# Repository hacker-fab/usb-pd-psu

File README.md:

# USB PD PSU
Inspired by the [PocketPD project](https://github.com/CentyLab/PocketPD).  
Adjustable DC power supply based on AVS/PPS USB PD protocols. 
Uses the TPS26750A USB PD controller to handle up to 240W.

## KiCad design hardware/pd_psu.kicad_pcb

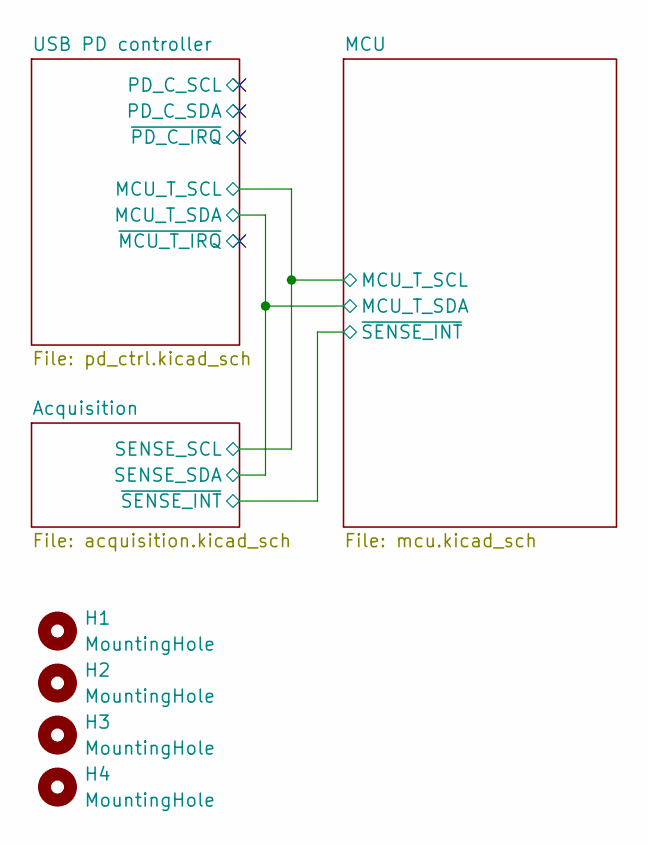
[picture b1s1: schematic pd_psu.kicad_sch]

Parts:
H1, H2, H3, H4: MountingHole; MountingHole_2.7mm_M2.5

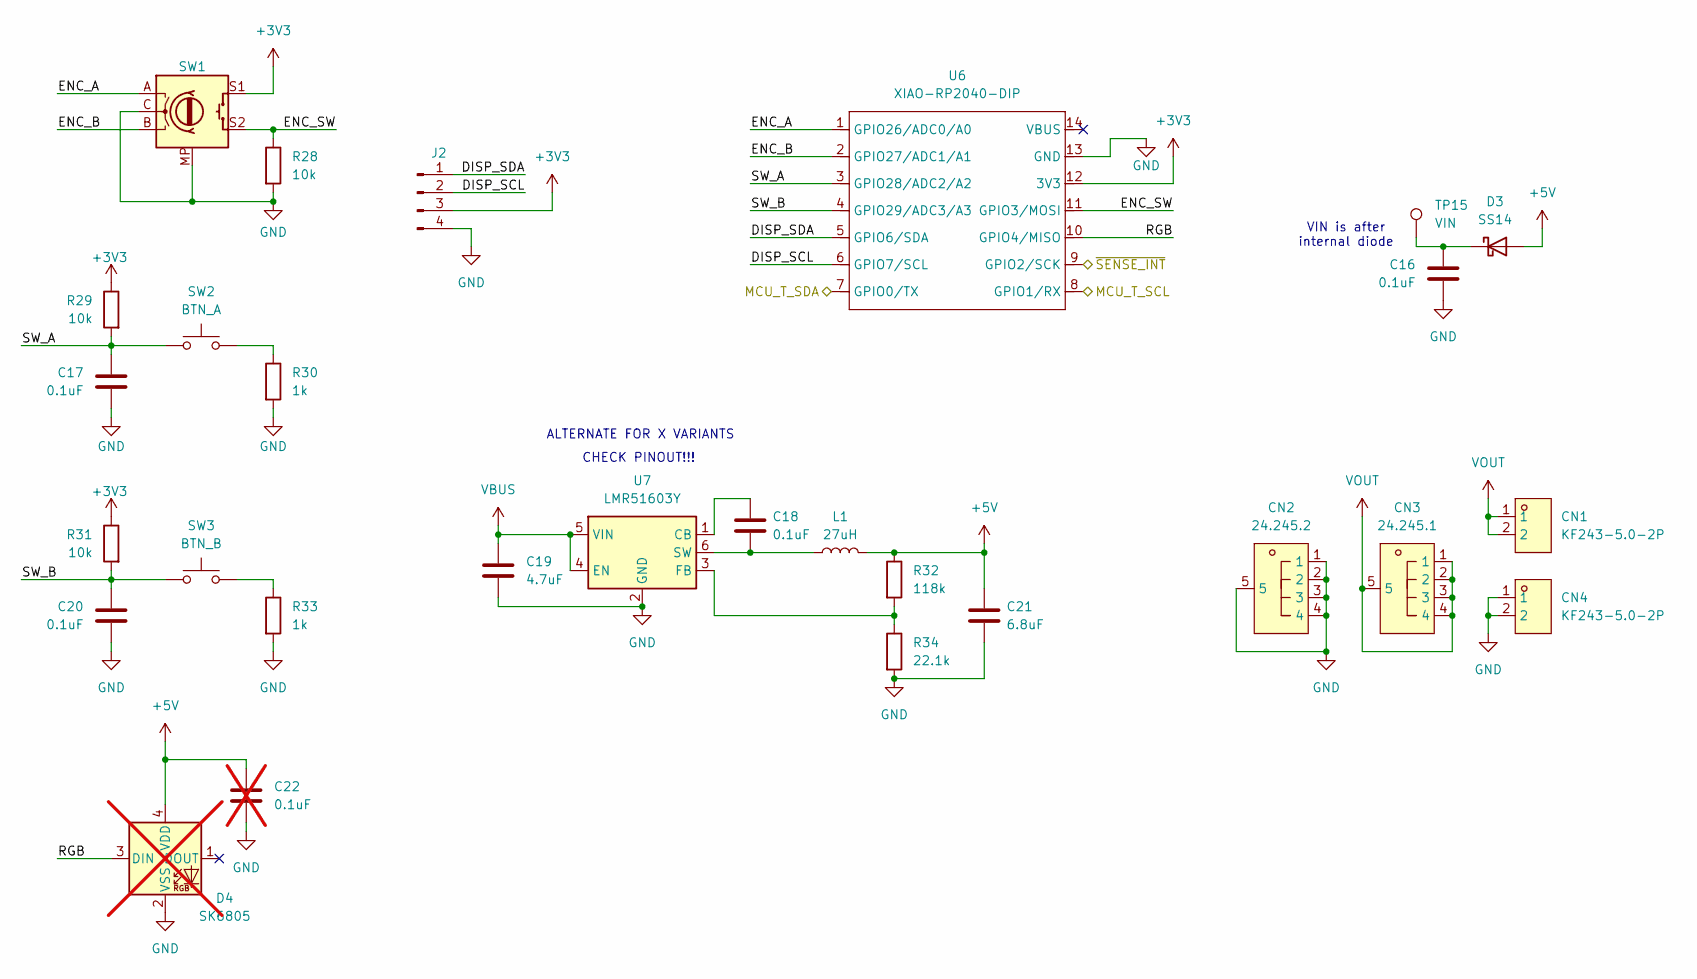
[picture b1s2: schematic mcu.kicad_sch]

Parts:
C16, C17, C20: 0.1uF; C_0603_1608Metric; LCSC ANY 16V
C18: 0.1uF; C_1206_3216Metric; LCSC C1945
C19: 4.7uF; C_1210_3225Metric; rating 100v; LCSC C381466
C21: 6.8uF; C_0603_1608Metric; LCSC C338096
C22: 0.1uF; C_0603_1608Metric; LCSC ANY 16V; not fitted
CN1, CN4: KF243-5.0-2P; CONN-TH_P5.00_KF243-5.0-2P; MPN KF243-5.0-2P; LCSC Part C475222
CN2: 24.245.2; ANT-TH_L33.0-W12.0_RED; MPN 24.245.2; LCSC Part C7437327
CN3: 24.245.1; ANT-TH_L33.0-W12.0_RED; MPN 24.245.1; LCSC Part C7437326
D3: SS14; D_SMA
D4: SK6805; LED_SK6805_PLCC4_2.4x2.7mm_P1.3mm; not fitted
J2: Conn_01x04_Pin; PinHeader_1x04_P2.54mm_Vertical
L1: 27uH; IND-SMD_L4.7-W4.7; LCSC C2983066 OR C187286
R28, R29, R31: 10k; R_0603_1608Metric
R30, R33: 1k; R_0603_1608Metric
R32: 118k; R_0603_1608Metric; LCSC C5126230
R34: 22.1k; R_0603_1608Metric; LCSC C2960862
SW1: RotaryEncoder_Switch_MP; RotaryEncoder_EC11B-Horizontal-Dual; LCSC C470710
SW2: BTN_A; SW-SMD_L6.0-W6.0-LS6.6; LCSC C398058
SW3: BTN_B; SW-SMD_L6.0-W6.0-LS6.6; LCSC C398058
TP15: VIN; TestPoint_Pad_D1.5mm
U6: XIAO-RP2040-DIP
U7: LMR51603Y; SOT-23-6; LCSC C43351621

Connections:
+3V3: J2.3, R29.1, R31.1, SW1.S1, U6.12 (3V3); also elsewhere on the board
+5V: C21.1, C22.1, D3.2 (A), D4.4 (VDD), L1.2, R32.1; also elsewhere on the board
/Acquisition/~SENSE_INT: U6.9 (GPIO2/SCK); also elsewhere on the board
/MCU/DISP_SCL: J2.2, U6.6 (GPIO7/SCL)
/MCU/DISP_SDA: J2.1, U6.5 (GPIO6/SDA)
/MCU/ENC_A: SW1.A, U6.1 (GPIO26/ADC0/A0)
/MCU/ENC_B: SW1.B, U6.2 (GPIO27/ADC1/A1)
/MCU/ENC_SW: R28.1, SW1.S2, U6.11 (GPIO3/MOSI)
/MCU/RGB: D4.3 (DIN), U6.10 (GPIO4/MISO)
/MCU/SW_A: C17.1, R29.2, SW2.1, U6.3 (GPIO28/ADC2/A2)
/MCU/SW_B: C20.1, R31.2, SW3.1, U6.4 (GPIO29/ADC3/A3)
/USB PD controller/MCU_T_SCL: U6.8 (GPIO1/RX); also elsewhere on the board
/USB PD controller/MCU_T_SDA: U6.7 (GPIO0/TX); also elsewhere on the board
GND: C16.2, C17.2, C19.2, C20.2, C21.2, C22.2, CN2.1, CN2.2, CN2.3, CN2.4, CN2.5, CN4.1, CN4.2, D4.2 (VSS), J2.4, R28.2, R30.2, R33.2, R34.2, SW1.C, SW1.MP, U6.13 (GND), U7.2 (GND); also elsewhere on the board
unnamed: C16.1, D3.1 (K), TP15.1 (1_1)
unnamed: R30.1, SW2.2
unnamed: R33.1, SW3.2
unnamed: C18.1, U7.1 (CB)
unnamed: R32.2, R34.1, U7.3 (FB)
unnamed: C18.2, L1.1, U7.6 (SW)
VBUS: C19.1, U7.4 (EN), U7.5 (VIN); also elsewhere on the board
VOUT: CN1.1, CN1.2, CN3.1, CN3.2, CN3.3, CN3.4, CN3.5; also elsewhere on the board

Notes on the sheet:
CHECK PINOUT!!!
ALTERNATE FOR X VARIANTS
VIN is after internal diode

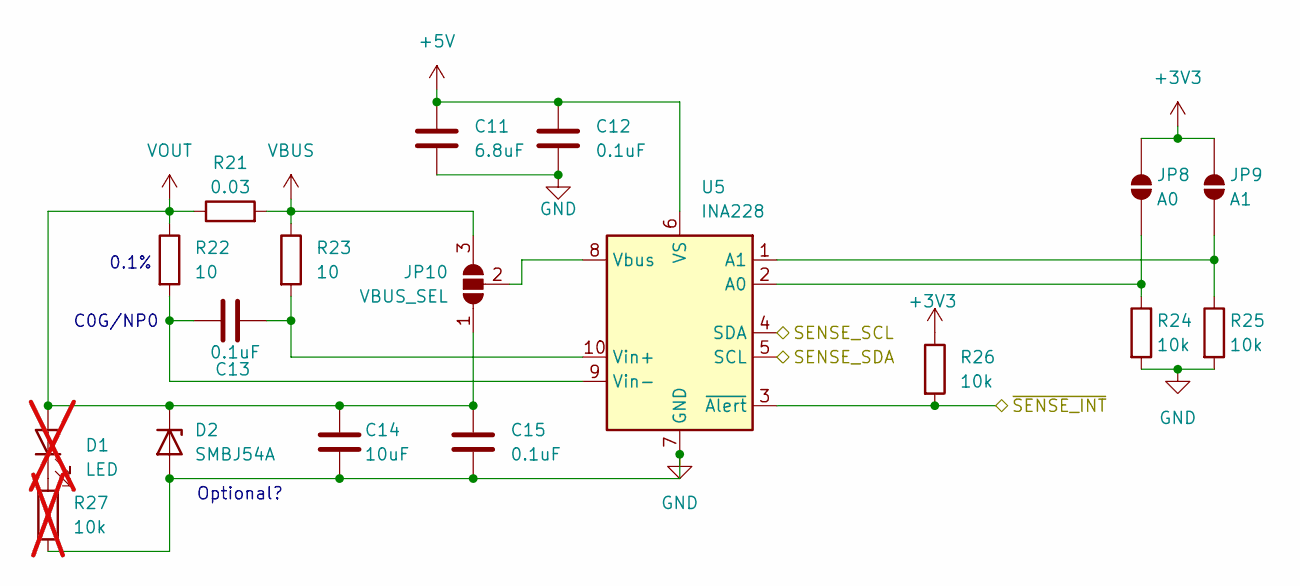
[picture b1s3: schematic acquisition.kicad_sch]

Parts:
C11: 6.8uF; C_0603_1608Metric; LCSC C338096
C12: 0.1uF; C_0603_1608Metric
C13: 0.1uF; C_1206_3216Metric; LCSC C1864297
C14: 10uF; C_1210_3225Metric
C15: 0.1uF; C_1206_3216Metric; rating 100V; LCSC C1945
D1: LED; LED_0603_1608Metric; not fitted
D2: SMBJ54A; D_SMB; LCSC C49066951
JP8: A0; SolderJumper-2_P1.3mm_Open_TrianglePad1.0x1.5mm
JP9: A1; SolderJumper-2_P1.3mm_Open_TrianglePad1.0x1.5mm
JP10: VBUS_SEL; SolderJumper-3_P2.0mm_Open_TrianglePad1.0x1.5mm
R21: 0.03; R_2512_6332Metric; LCSC C22468062
R22, R23: 10; R_0603_1608Metric; LCSC C861082
R24, R25, R26: 10k; R_0603_1608Metric
R27: 10k; R_0603_1608Metric; not fitted
U5: INA228; TSSOP-10_3x3mm_P0.5mm

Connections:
+3V3: JP8.1 (A), JP9.1 (A), R26.1; also elsewhere on the board
+5V: C11.1, C12.1, U5.6 (VS); also elsewhere on the board
/Acquisition/~SENSE_INT: R26.2, U5.3 (~Alert); also elsewhere on the board
/USB PD controller/MCU_T_SCL: U5.4 (SDA); also elsewhere on the board
/USB PD controller/MCU_T_SDA: U5.5 (SCL); also elsewhere on the board
GND: C11.2, C12.2, C14.2, C15.2, D2.2 (A), R24.2, R25.2, R27.2, U5.7 (GND); also elsewhere on the board
unnamed: D1.1 (K), R27.1
unnamed: JP8.2 (B), R24.1, U5.2 (A0)
unnamed: JP9.2 (B), R25.1, U5.1 (A1)
unnamed: JP10.2 (C), U5.8 (Vbus)
unnamed: C13.2, R23.2, U5.10 (Vin+)
unnamed: C13.1, R22.2, U5.9 (Vin-)
VBUS: JP10.3 (B), R21.2, R23.1; also elsewhere on the board
VOUT: C14.1, C15.1, D1.2 (A), D2.1 (K), JP10.1 (A), R21.1, R22.1; also elsewhere on the board

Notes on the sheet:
C0G/NP0
Optional?
0.1%

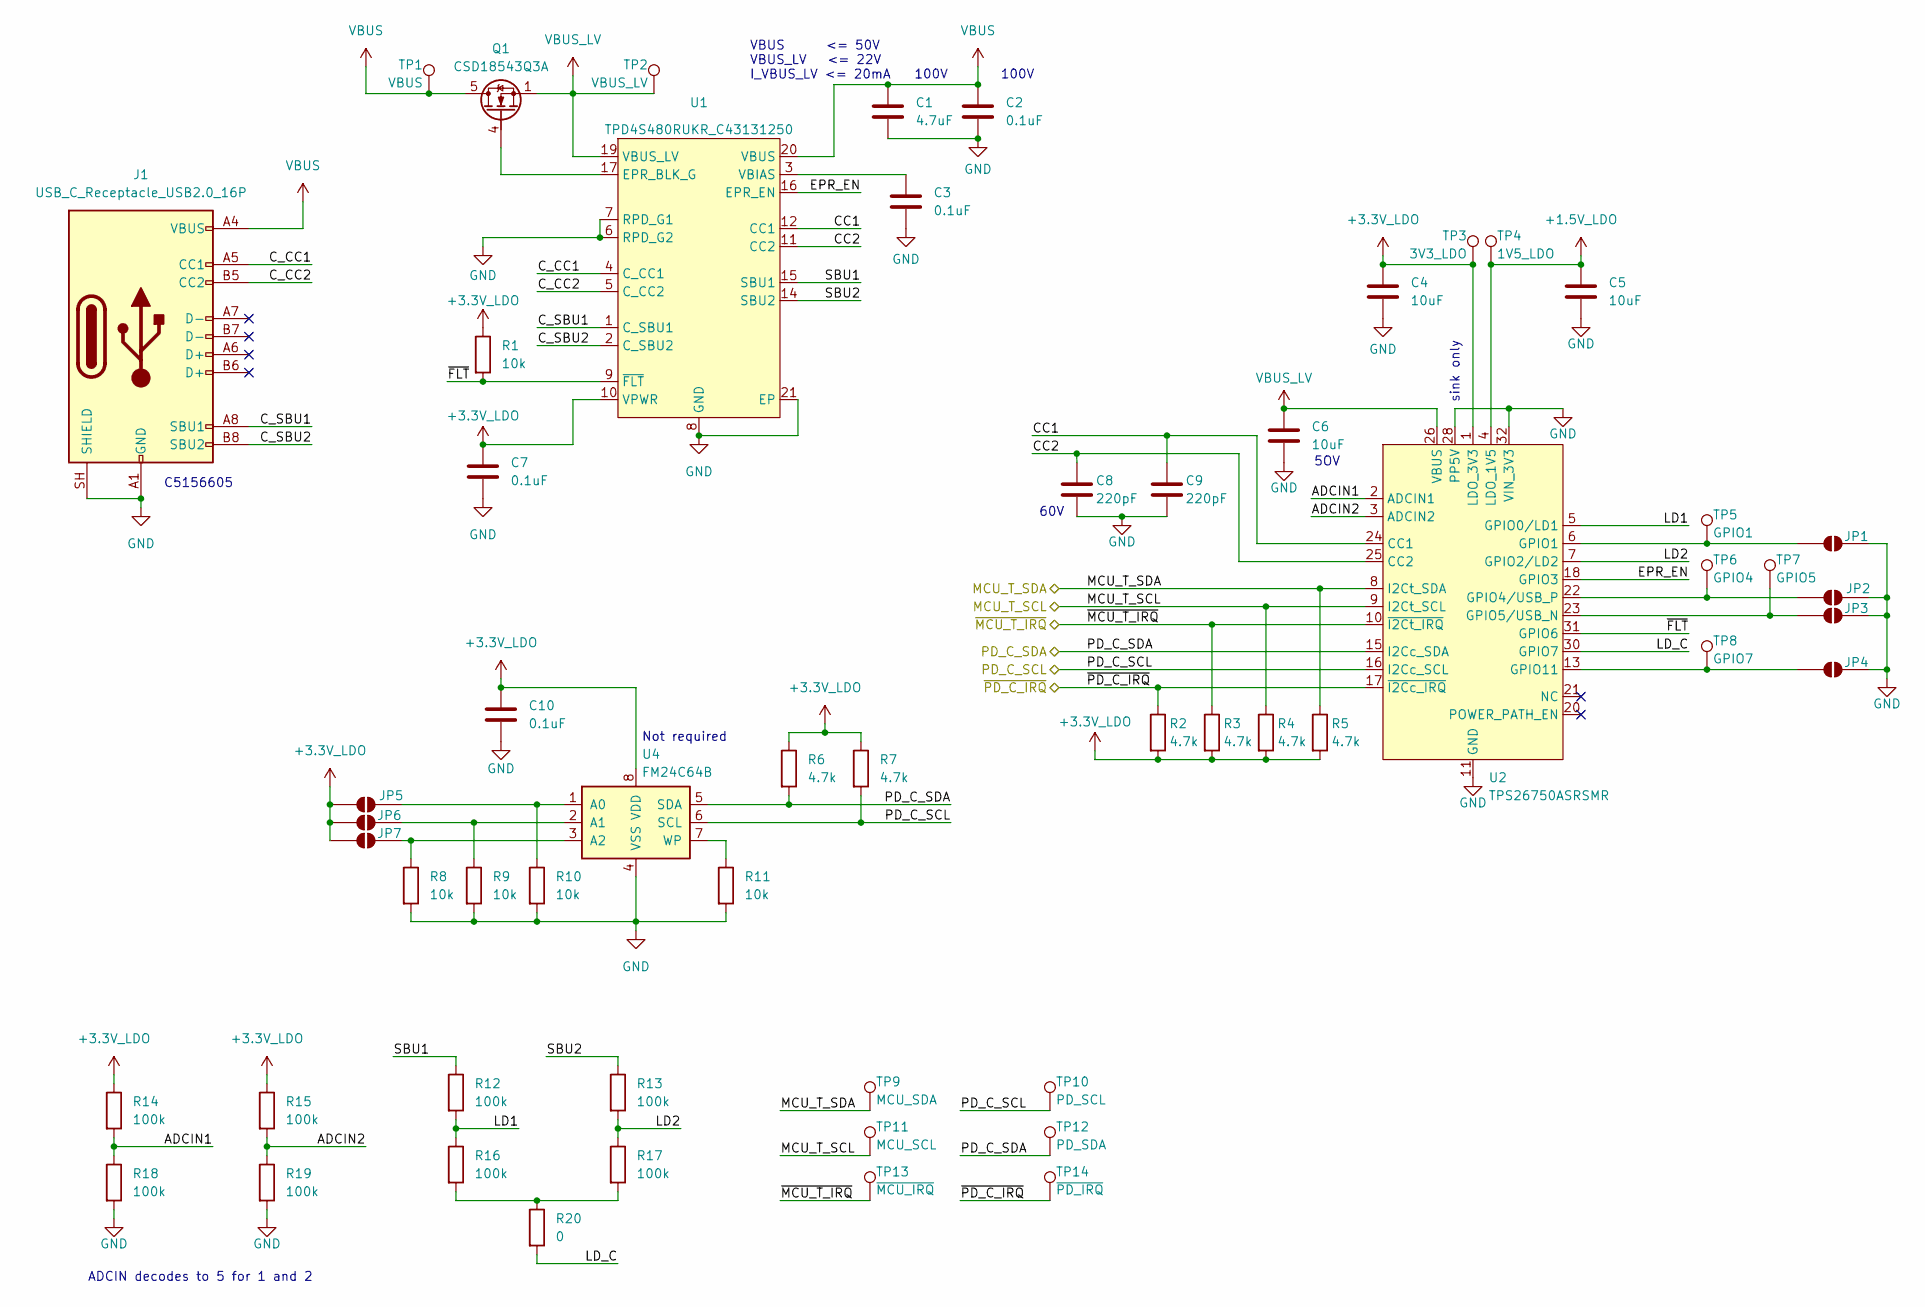
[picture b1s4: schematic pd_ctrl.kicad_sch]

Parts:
C1: 4.7uF; C_1210_3225Metric; rating 100v; LCSC C381466
C2: 0.1uF; C_1206_3216Metric; rating 100V; LCSC C1945
C3: 0.1uF; C_1206_3216Metric; LCSC C1945
C4, C5: 10uF; C_0805_2012Metric; LCSC C15850
C6: 10uF; C_0805_2012Metric; LCSC C22367830
C7, C10: 0.1uF; C_0603_1608Metric; LCSC ANY 16V
C8, C9: 220pF; C_0603_1608Metric; LCSC C106210
J1: USB_C_Receptacle_USB2.0_16P; TYPE-C-USB-SMD_QCHT-143
JP1, JP2, JP3, JP4, JP5, JP6, JP7: SolderJumper_2_Open; SolderJumper-2_P1.3mm_Open_TrianglePad1.0x1.5mm
Q1: CSD18543Q3A; VSON-8_3.3x3.3mm_P0.65mm_NexFET; LCSC C840100
R1, R8, R9, R10, R11: 10k; R_0603_1608Metric
R2, R3, R4, R5, R6, R7: 4.7k; R_0603_1608Metric
R12, R13, R14, R15, R16, R17, R18, R19: 100k; R_0603_1608Metric
R20: 0; R_0603_1608Metric
TP1: VBUS; TestPoint_Pad_D1.5mm
TP2: VBUS_LV; TestPoint_Pad_D1.5mm
TP3: 3V3_LDO; TestPoint_Pad_D1.5mm
TP4: 1V5_LDO; TestPoint_Pad_D1.5mm
TP5: GPIO1; TestPoint_Pad_D1.5mm
TP6: GPIO4; TestPoint_Pad_D1.5mm
TP7: GPIO5; TestPoint_Pad_D1.5mm
TP8: GPIO7; TestPoint_Pad_D1.5mm
TP9: MCU_SDA; TestPoint_Pad_D1.5mm
TP10: PD_SCL; TestPoint_Pad_D1.5mm
TP11: MCU_SCL; TestPoint_Pad_D1.5mm
TP12: PD_SDA; TestPoint_Pad_D1.5mm
TP13: ~{MCU_IRQ}; TestPoint_Pad_D1.5mm
TP14: ~{PD_IRQ}; TestPoint_Pad_D1.5mm
U1: TPD4S480RUKR_C43131250; WQFN-20_L3.0-W3.0-P0.40-BL-EP1.7; MPN TPD4S480RUKR; LCSC Part C43131250
U2: TPS26750ASRSMR; QFN-32_L4.0-W4.0-P0.40-BL-EP2.8; MPN TPS26750SRSMR; LCSC Part C42166327
U4: FM24C64B; SOIC-8_3.9x4.9mm_P1.27mm; LCSC C79988

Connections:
+1.5V_LDO: C5.1, TP4.1, U2.4 (LDO_1V5); also elsewhere on the board
+3.3V_LDO: C4.1, C7.1, C10.1, JP5.1 (A), JP6.1 (A), JP7.1 (A), R1.1, R2.2, R3.2, R4.2, R5.2, R6.1, R7.1, R14.1, R15.1, TP3.1, U1.10 (VPWR), U2.1 (LDO_3V3), U4.8 (VDD); also elsewhere on the board
/USB PD controller/ADCIN1: R14.2, R18.1, U2.2 (ADCIN1)
/USB PD controller/ADCIN2: R15.2, R19.1, U2.3 (ADCIN2)
/USB PD controller/CC1: C9.1, U1.12 (CC1), U2.24 (CC1)
/USB PD controller/CC2: C8.1, U1.11 (CC2), U2.25 (CC2)
/USB PD controller/C_CC1: J1.A5 (CC1), U1.4 (C_CC1)
/USB PD controller/C_CC2: J1.B5 (CC2), U1.5 (C_CC2)
/USB PD controller/C_SBU1: J1.A8 (SBU1), U1.1 (C_SBU1)
/USB PD controller/C_SBU2: J1.B8 (SBU2), U1.2 (C_SBU2)
/USB PD controller/D_+: J1.A6 (D+), J1.B6 (D+)
/USB PD controller/D_-: J1.A7 (D-), J1.B7 (D-)
/USB PD controller/EPR_EN: U1.16 (EPR_EN), U2.18 (GPIO3)
/USB PD controller/LD1: R12.2, R16.1, U2.5 (GPIO0/LD1)
/USB PD controller/LD2: R13.2, R17.1, U2.7 (GPIO2/LD2)
/USB PD controller/LD_C: R20.2, U2.30 (GPIO7)
/USB PD controller/MCU_T_SCL: R4.1, TP11.1, U2.9 (I2Ct_SCL); also elsewhere on the board
/USB PD controller/MCU_T_SDA: R5.1, TP9.1, U2.8 (I2Ct_SDA); also elsewhere on the board
/USB PD controller/PD_C_SCL: R7.2, TP10.1, U2.16 (I2Cc_SCL), U4.6 (SCL); also elsewhere on the board
/USB PD controller/PD_C_SDA: R6.2, TP12.1, U2.15 (I2Cc_SDA), U4.5 (SDA); also elsewhere on the board
/USB PD controller/SBU1: R12.1, U1.15 (SBU1)
/USB PD controller/SBU2: R13.1, U1.14 (SBU2)
/USB PD controller/~FLT: R1.2, U1.9 (~FLT), U2.31 (GPIO6)
/USB PD controller/~MCU_T_IRQ: R3.1, TP13.1, U2.10 (~I2Ct_IRQ)
/USB PD controller/~PD_C_IRQ: R2.1, TP14.1, U2.17 (~I2Cc_IRQ)
GND: C1.2, C2.2, C3.2, C4.2, C5.2, C6.2, C7.2, C8.2, C9.2, C10.2, J1.A1 (GND), J1.A12 (GND), J1.B1 (GND), J1.B12 (GND), J1.SH (SHIELD), JP1.2 (B), JP2.2 (B), JP3.2 (B), JP4.2 (B), R8.2, R9.2, R10.2, R11.2, R18.2, R19.2, U1.6 (RPD_G2), U1.7 (RPD_G1), U1.8 (GND), U1.13 (GND), U1.18 (GND), U1.21 (EP), U2.11 (GND), U2.12 (GND), U2.14 (GND), U2.19 (GND), U2.28 (PP5V), U2.29 (PP5V), U2.32 (VIN_3V3), U2.33 (GND), U4.4 (VSS); also elsewhere on the board
unnamed: JP1.1 (A), TP5.1 (1_1), U2.6 (GPIO1)
unnamed: JP2.1 (A), TP6.1 (1_1), U2.22 (GPIO4/USB_P)
unnamed: JP3.1 (A), TP7.1 (1_1), U2.23 (GPIO5/USB_N)
unnamed: JP4.1 (A), TP8.1 (1_1), U2.13 (GPIO11)
unnamed: JP5.2 (B), R10.1, U4.1 (A0)
unnamed: JP6.2 (B), R9.1, U4.2 (A1)
unnamed: JP7.2 (B), R8.1, U4.3 (A2)
unnamed: Q1.4 (G), U1.17 (EPR_BLK_G)
unnamed: R16.2, R17.2, R20.1
unnamed: C3.1, U1.3 (VBIAS)
unnamed: R11.1, U4.7 (WP)
VBUS: C1.1, C2.1, J1.A4 (VBUS), J1.A9 (VBUS), J1.B4 (VBUS), J1.B9 (VBUS), Q1.5 (D), TP1.1, U1.20 (VBUS); also elsewhere on the board
VBUS_LV: C6.1, Q1.1 (S), Q1.2 (S), Q1.3 (S), TP2.1, U1.19 (VBUS_LV), U2.26 (VBUS), U2.27 (VBUS); also elsewhere on the board

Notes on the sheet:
C5156605
100V
sink only
5OV
ADCIN decodes to 5 for 1 and 2
VBUS <= 50V VBUS_LV <= 22V I_VBUS_LV <= 20mA
60V
Not required

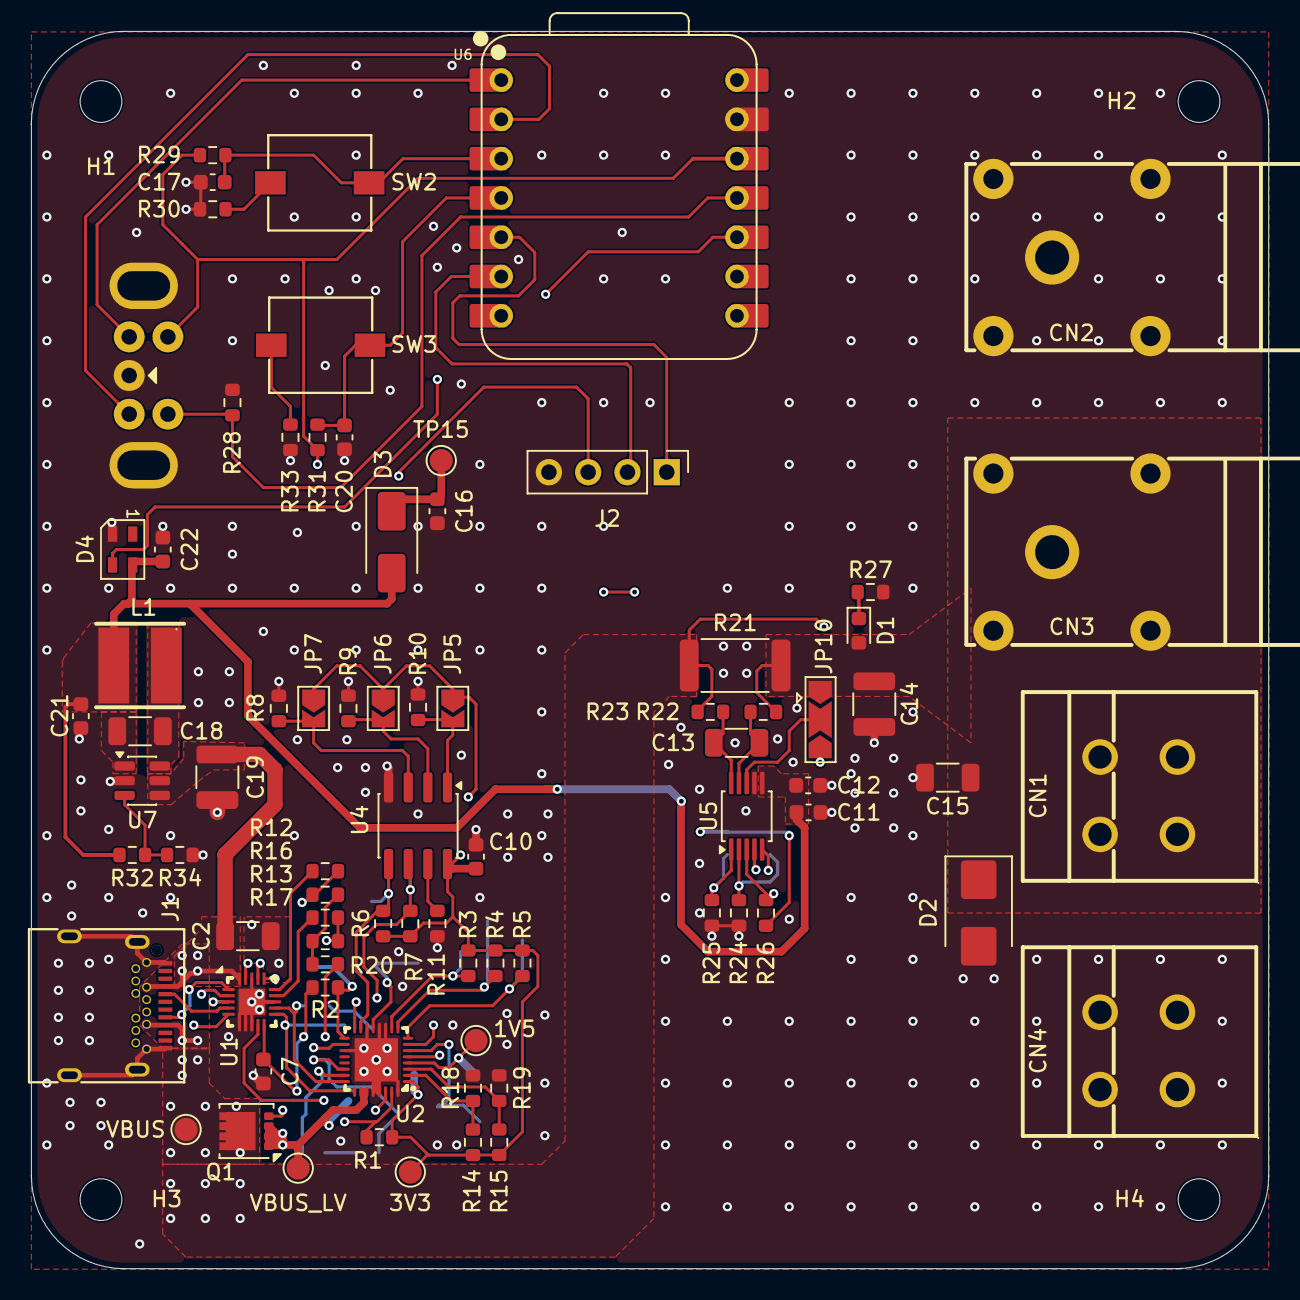
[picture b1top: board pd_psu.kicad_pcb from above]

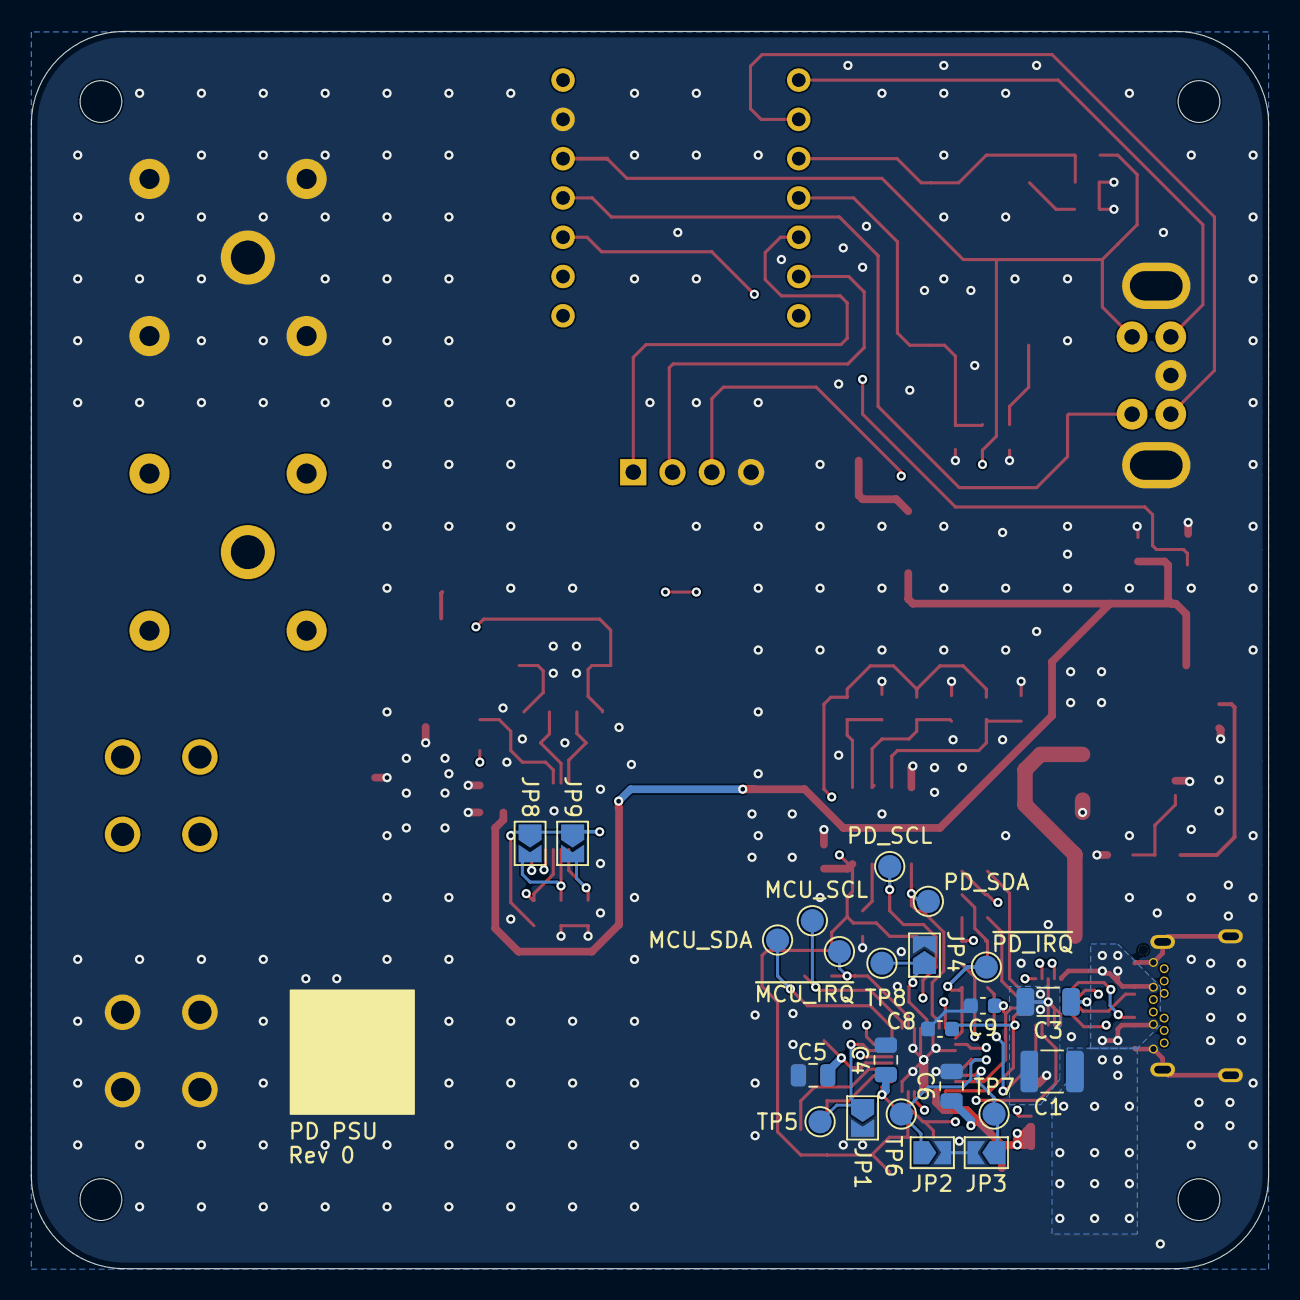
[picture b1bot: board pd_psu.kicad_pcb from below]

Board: 4 copper layers, 80.0 x 80.0 mm, 104 parts (21 on the bottom side), 63 nets.

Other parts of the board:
1V5: 1V5_LDO; TestPoint_Pad_D1.5mm
3V3: 3V3_LDO; TestPoint_Pad_D1.5mm
MCU_SCL: MCU_SCL; TestPoint_Pad_D1.5mm
MCU_SDA: MCU_SDA; TestPoint_Pad_D1.5mm
PD_SCL: PD_SCL; TestPoint_Pad_D1.5mm
PD_SDA: PD_SDA; TestPoint_Pad_D1.5mm
VBUS: VBUS; TestPoint_Pad_D1.5mm
VBUS_LV: VBUS_LV; TestPoint_Pad_D1.5mm

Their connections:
+1.5V_LDO: 1V5.1 (1_1); also elsewhere on the board
+3.3V_LDO: 3V3.1 (1_1); also elsewhere on the board
/USB PD controller/MCU_T_SCL: MCU_SCL.1 (1_1); also elsewhere on the board
/USB PD controller/MCU_T_SDA: MCU_SDA.1 (1_1); also elsewhere on the board
/USB PD controller/PD_C_SCL: PD_SCL.1 (1_1); also elsewhere on the board
/USB PD controller/PD_C_SDA: PD_SDA.1 (1_1); also elsewhere on the board
VBUS: VBUS.1 (1_1); also elsewhere on the board
VBUS_LV: VBUS_LV.1 (1_1); also elsewhere on the board
